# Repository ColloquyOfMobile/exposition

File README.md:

# exposition
Colloquy of Mobiles for exposition in ZKM

## Hardware
- `CAD/KiCad/tj_brain`: **TJ Brain**, one Teensy 4.1 controller per unit (female 1-3, male 1-2, bar).
  It brings back T. J. McLeish's distributed 2018 architecture and has a DA-15 body connector
  compatible with the female harnesses.
- `CAD/KiCad/tj_backplane`: **TJ Backplane**, the 12V / 5V splitter (fused, with LEDs) that feeds the
  brains and the USB hub.
- `CAD/KiCad/electronic box`: the previous centralised board (Arduino Mega + U2D2).
- `Source code/Teensy/tj_brain_test`: Teensy pin map and bring-up test sketch for the TJ Brain.

## Todo
In KiCad:
- Choose the footprint for power supply capacitor.
- Check dimension of jack barrel.

## Todo

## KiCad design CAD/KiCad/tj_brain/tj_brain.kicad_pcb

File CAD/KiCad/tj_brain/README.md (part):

# TJ Brain – one Teensy 4.1 brain per unit

This board brings back the distributed 2018 architecture of T. J. McLeish
(one controller per mobile) with a Teensy 4.1. The **same board** is used for
the three females, the two males and the bar. A DIP switch sets which unit it is.

```
            computer (Python server)
                 │ USB
        7-port powered USB 2.0 hub ───────────────┐ one USB cable per brain
                 │                                │ (Teensy micro-USB)
   12V PSU ──┐   │                                ▼
   5V  PSU ──┴─► TJ BACKPLANE ──Mini-Fit Jr 4p──► TJ BRAIN ×6 (F1 F2 F3 M1 M2 BAR) + spare
                 (fused splitter,                    │
                  powers the hub)                    ├─ DXL1-3 (JST EH) ─ Dynamixel X TTL
                                                     ├─ NP1-4 (pluggable 5.08) ─ NeoPixels
                                                     ├─ SPK, LS1-4, MIC, STATE1-2 (JST XH)
                                                     └─ BODY DA-15 ─ into the female (or male) body
```

* Schematic: `tj_brain.kicad_sch` (9 sheets), PCB: `tj_brain.kicad_pcb`
  (180 × 136 mm, 2 layers, 1.6 mm, 1 oz copper is enough on this board).
* Manufacturing files in `fab/`: Gerbers and drill files (zipped), pick-and-place, BOM,
  schematic PDF, assembly drawing, top and bottom renders.
* Custom parts (Teensy 4.1 socket, SparkFun TPA2005D1 breakout) are in `../tj_library`.
* Everything is generated by `../generator` (see the last section). Edit the generator
  and regenerate rather than editing the KiCad files by hand, or the next run overwrites
  your changes.

## Connectors

| Ref | Connector | Pins |
|-----|-----------|------|
| J1 | Molex Mini-Fit Jr 5569 right-angle 2×2, from the backplane | 1 = +12V, 2 = +5V, 3 = GND, 4 = GND |
| U1 | Teensy 4.1 on 2× 1×24 female headers | USB from the hub goes straight into the Teensy |
| J20 BODY | DA-15 **male** (pins on the board), right-angle | see table below |
| J3–J5 DXL1–3 | JST EH B3B-EH-A (ROBOTIS X-series TTL) | 1 GND, 2 +12V, 3 DATA |
| J6–J9 NP1–4 | Phoenix MSTBA 2,5/3-G-5,08 (plug MSTB 2,5/3-ST-5,08) | 1 +5V, 2 DIN, 3 GND |
| J11 SPK | Phoenix MSTBA 2,5/2-G-5,08 | 1 SPK+, 2 SPK− |
| J13–J16 LS1–4 | JST XH 3p | 1 sensor VCC (5V, or 3V3 via JP4), 2 GND, 3 signal 0–5V |
| J12 MIC | JST XH 3p | 1 VCC (5V, or 3V3 via JP3), 2 GND, 3 MAX9814 OUT |
| J17/J18 STATE1/2 | JST XH 2p | 1 switched +5V through 150 Ω, 2 GND |
| J10 EXT AMP | 1×4 header | 1 line out (AC coupled), 2 GND, 3 +5V, 4 GND |
| J2 EXP | 2×5 header | 3V3, 5V, SDA, SCL, A9, A11, D26, D27, A16, A17 |
| J19 PROBE | 1 pin | logic probe input for the PROBE LED (0–12 V) |

### BODY DA-15 (J20)

Pins 4, 5, 6, 7, 8, 12, 13, 14 and 15 match the female D-subs of the old electronic box
(J1/J5 there). The existing female body harnesses plug in unchanged. Pins 1, 2, 3, 9, 10
and 11 were unused there and now carry what a male body needs.

| Pin | Signal | Female use | Male use |
|----:|--------|------------|----------|
| 1 | LS2 | – | photosensor B |
| 2 | LS3 | – | photosensor C |
| 3 | LS4 | – | photosensor D |
| 4 | SPK− | speaker | speaker |
| 5 | LS1 | photosensor | photosensor A |
| 6 | MIC | microphone module out | microphone module out |
| 7 | +12V (PTC 3 A, F1) | mirror Dynamixel | – |
| 8 | GND | | |
| 9 | NP2 | – | up ring NeoPixels |
| 10 | STATE1 | – | state LED / backlight (switched 5V, 150 Ω) |
| 11 | AUX (analog, clamped) | spare | spare |
| 12 | SPK+ | speaker | speaker |
| 13 | NP1 | body NeoPixel strip | body NeoPixel strip |
| 14 | DXL DATA | mirror Dynamixel | – |
| 15 | +5V (PTC 4 A, F2) | NeoPixels, sensors, mic | NeoPixels, sensors, mic |
| shell | GND | | |

The board side is a **male** DA-15, the same as the footprint in the old electronic box.
Check this against your harness connectors before ordering.

## LEDs

| LED | Meaning |
|-----|---------|
| 12V, 5V, 3V3 | rail present on the board |
| BODY12, BODY5 | rail present on the DA-15 after its PTC (off = PTC tripped) |
| HB, HOST, ERR, USER | driven by firmware (heartbeat, host connected, error, free) |
| NP1–NP4 | data on that NeoPixel output (hardware pulse stretcher, ~50 ms per frame) |
| DXL TX | the Teensy is transmitting on the Dynamixel bus |
| DXL BUS | any traffic on the Dynamixel bus (TX or replies) |
| TONE | tone output active |
| PROBE | free logic probe: touch J19 to any 0–12 V signal |
| LIGHT1–4 | sensor above the threshold set with trimmer TH1–4 (LM339). Use it to aim the beams |
| STATE1, STATE2 | state output switched on (brightness follows PWM) |

## Teensy 4.1 pin map

The pin map is also in `Source code/Teensy/tj_brain_test/tj_brain_pins.h`.

| Pin | Function | Pin | Function |
|----:|----------|----:|----------|
| 0 / 1 | Dynamixel RX1 / TX1 | 14 (A0) | LS1 |
| 2 | Dynamixel DIR (1 = TX) | 15 (A1) | LS2 |
| 3 / 4 | STATE1 / STATE2 (PWM) | 16 (A2) | MIC |
| 5 | AMP_EN (amp shutdown, high = on) | 17 (A3) | LS3 |
| 6, 7, 11, 28 | unit ID bits 0–3 (SW1) | 18 / 19 | SDA / SCL (J2) |
| 8 | NP1 (TX2) | 20 (A6) | LS4 |
| 29 | NP2 (TX7) | 21 (A7) | MSGEQ7 OUT |
| 35 | NP3 (TX8) | 22 (A8) | AUX (DA-15 pin 11) |
| 24 | NP4 (TX6) | 23, 25, 26, 27, 40, 41 | expansion J2 |
| 9 / 10 | MSGEQ7 STROBE / RESET | 30, 31, 32, 37 | LEDs HB, HOST, ERR, USER |
| 12 | AUDIO (tone() or MQSL) | 13, 33, 34, 36, 38, 39 | free (13 = on-board LED) |

The four NeoPixel pins are serial TX pins, so the `WS2812Serial` (DMA, non-blocking) or
`OctoWS2811` libraries can drive them without stopping interrupts. The Dynamixel bus works
with `Dynamixel2Arduino dxl(Serial1, 2);`.

## Unit ID (SW1)

Switch 1 is bit 0, and a switch set to ON counts as 1. The firmware reads it with
`readUnitId()` and reports its role to the host. The host can then open the right serial
port for each unit without having to remember port names.

| ID | Unit | SW1 1-2-3-4 | Dynamixel ids (unchanged) |
|---:|------|-------------|---------------------------|
| 1 | female1 | ON off off off | 1 body, 2 mirror |
| 2 | female2 | off ON off off | 3, 4 |
| 3 | female3 | ON ON off off | 5, 6 |
| 4 | male1 | off off ON off | 7 |
| 5 | male2 | ON off ON off | 8 |
| 6 | bar | off ON ON off | 9 |

## Per-unit build

| | Female 1–3 | Male 1–2 | Bar |
|---|---|---|---|
| Where | static part, DA-15 cable into the rotating body | on the bar / male static part | bar |
| DXL1 | body rotation motor | male rotation motor | bar motor |
| DA-15 DXL | mirror motor (inside the body) | – | – |
| NP1 | body strip, 50 RGBW | body strip, 40 RGBW (ring + drive) | – |
| NP2 | – | up ring, 12 RGBW | – |
| LS1–4 | LS1 | A–D | – |
| MIC / SPK | yes | yes | – |
| STATE1 | – | backlight (KWB-R8445W) | – |
| Tone filter | values for the unit's band | values for the unit's band | – |
| May be left unpopulated | – | – | U5 amp, U6 MSGEQ7, U7 LM339 and their parts |

### Tone filter (R23 = R24, C10 = C11)

These values come from T. Erforth's "Pask redesign" (Table 2). The board default is the
1 kHz set. Fit the set that matches each unit's band.

| Band | R | C |
|-----:|---|---|
| 160 Hz | 2k2 | 470 nF |
| 400 Hz | 2k | 220 nF |
| 1 kHz | 1k2 | 150 nF |
| 2.5 kHz | 1k8 | 47 nF |
| 6.25 kHz | 2k2 | 10 nF |

* If the Teensy generates a sine wave instead (Audio library on MQS pin 12), use
  2k2 / 10 nF for every unit. The filter then only removes the MQS carrier.
* The divider is 22k / 6k8 instead of Thomas's 22k / 3k3. The Teensy swings 3.3 Vpp
  instead of 5 Vpp, so this ratio still gives about 330 mVpp at the amplifier.

### Amplifier options

* **On-board** (default): SparkFun BOB-11044 (TPA2005D1) plugged in at U5, volume on RV1.
  This is the same footprint as the electronic box. AMP_EN can mute it.
* **Amp next to the speaker** (Thomas's recommendation for the class-D EMI):
  1. Leave U5 out.
  2. Close JP1 and JP2. The DA-15 pins 12/4 then carry the line level (AC coupled) and GND.
  3. Power the GF1002 module in the body from DA-15 pin 15 (5V).
  4. Instead of steps 2–3, a module on the board can be wired to the EXT AMP header J10.

### Sensors and microphone

* The light sensor inputs accept 0–5 V modules, as in the old box. A 10k/18k divider keeps
  the ADC below 3.3 V.
* For a bare LDR, the 28 kΩ divider is the pull-down. Wire the LDR between VCC and the
  signal pin.
* Sensor VCC is 5V by default. Cut JP4 and bridge it to the 3V3 side for 3.3 V sensors.
  JP3 does the same for the microphone.
* The microphone input (MAX9814, bias 1.25 V, 2 Vpp) has a 1 kΩ resistor and a BAT54S
  clamp. It goes both to A2 and, through 22 kΩ + 10 nF, to the optional socketed MSGEQ7.
* The MSGEQ7 runs at 3.3 V, so its output fits the ADC. Pin 6 is decoupled with 100 nF
  as the datasheet requires; it is not tied to GND.

## Assembly notes

* **Teensy power**: VIN is fed from +5V through a B5819W Schottky diode. The VIN/VUSB
  trace on the Teensy can stay **uncut**: the diode keeps the backplane 5V and the PC
  USB 5V from feeding each other. The Teensy then runs from whichever supply is higher.
* Mount the Teensy on 2× 1×24 female headers. Its USB connector is at the board edge.
  Use a micro-USB cable with strain relief, and tie the cable to the enclosure.
* All SMD parts are 0805 / SOT-23 / SOIC on the top side with hand-solder pads. The
  MSGEQ7 is socketed.
* PTCs: F1 = Bourns MF-RHT300 (body 12V), F2 = MF-RHT400 (body 5V).
* Before plugging the body in, set the four LIGHT thresholds (TH1–4) with the sensors
  installed.
* Bring-up: flash `Source code/Teensy/tj_brain_test`. It prints the unit ID and all the
  analog inputs, pings Dynamixel ids 1–10, and blinks every activity LED.

## Verification done

* The schematic was exported to a netlist with `kicad-cli` and compared net-by-net with
  the design description. Every net matches.
* KiCad DRC on the PCB (`fab/tj_brain-drc-report.txt`): **0 errors, 0 unconnected pads**.
  52 silkscreen warnings remain (connector outlines past the board edge, a few overlapping
  labels). They are cosmetic.
* All 602 pads on the PCB were compared with the design description; every net matches.
* Not checked: the custom footprints (Teensy 4.1 and SparkFun breakout) against real
  parts, the D-sub gender against the existing harness, and the Mini-Fit orientation in
  the enclosure. Check these on the first board before a full run.

## Regenerating

```
cd CAD/KiCad/generator
python3 make_lib.py            # TJ symbol / footprint library
python3 build_brain_sch.py     # schematic + netlist self-check
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
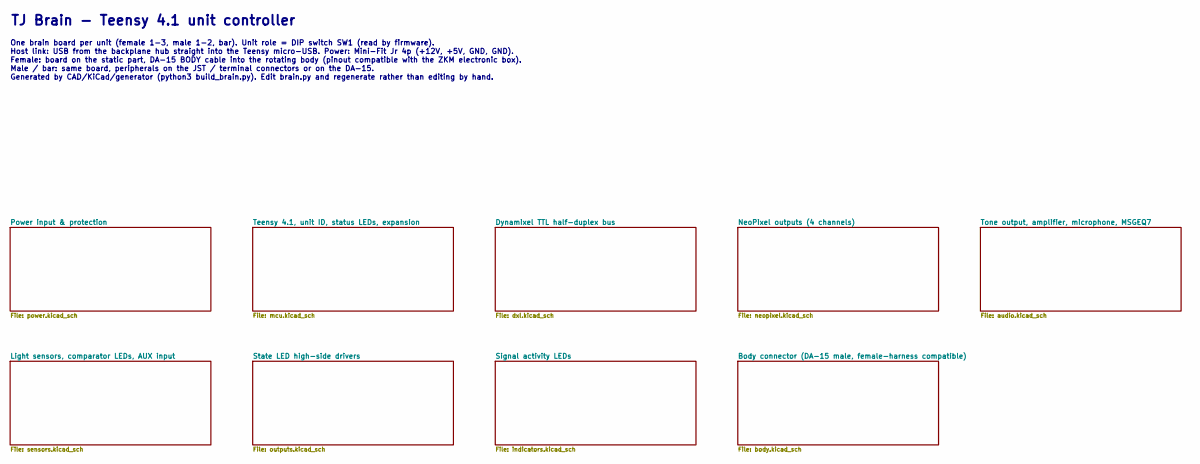
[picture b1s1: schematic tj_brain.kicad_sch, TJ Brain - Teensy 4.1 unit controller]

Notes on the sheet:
TJ Brain - Teensy 4.1 unit controller
One brain board per unit (female 1-3, male 1-2, bar). Unit role = DIP switch SW1 (read by firmware).
Host link: USB from the backplane hub straight into the Teensy micro-USB. Power: Mini-Fit Jr 4p (+12V, +5V, GND, GND).
Female: board on the static part, DA-15 BODY cable into the rotating body (pinout compatible with the ZKM electronic box).
Male / bar: same board, peripherals on the JST / terminal connectors or on the DA-15.
Generated by CAD/KiCad/generator (python3 build_brain.py). Edit brain.py and regenerate rather than editing by hand.

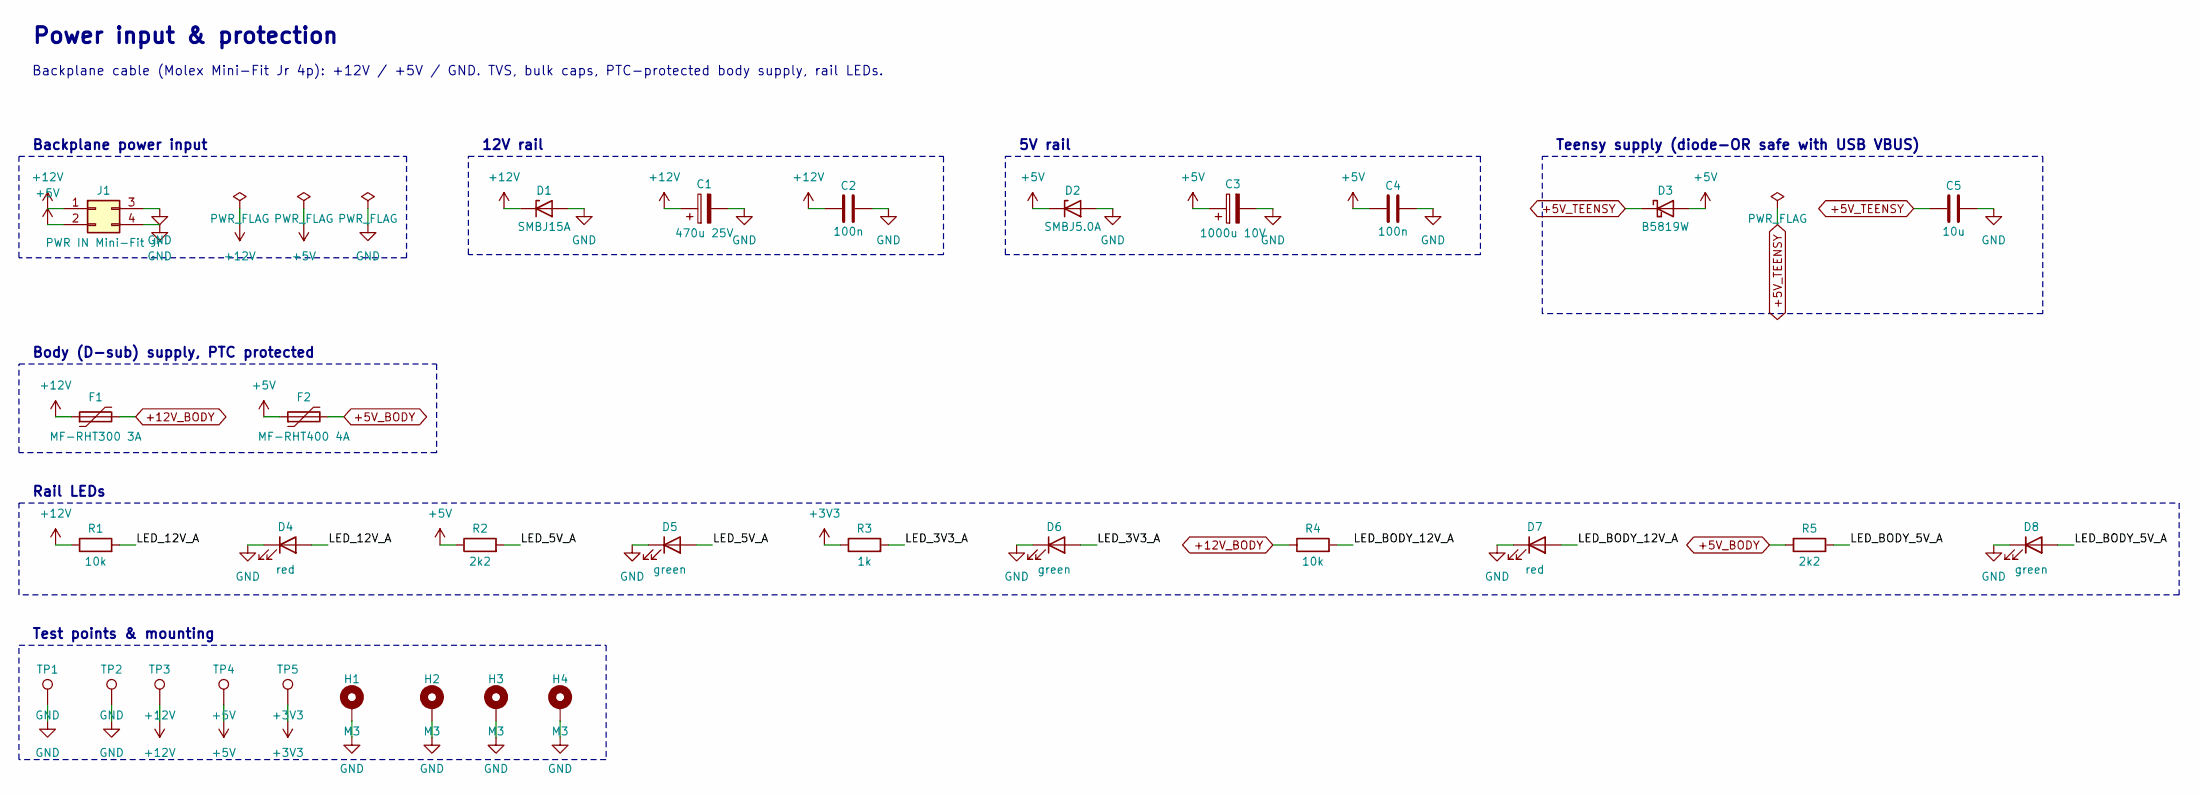
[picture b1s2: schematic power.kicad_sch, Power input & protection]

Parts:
C1: 470u 25V; CP_Radial_D10.0mm_P5.00mm
C2: 100n; C_1206_3216Metric_Pad1.33x1.80mm_HandSolder; Voltage 25V
C3: 1000u 10V; CP_Radial_D10.0mm_P5.00mm
C4: 100n; C_0805_2012Metric_Pad1.18x1.45mm_HandSolder
C5: 10u; C_1206_3216Metric_Pad1.33x1.80mm_HandSolder; Voltage 10V
D1: SMBJ15A; D_SMB
D2: SMBJ5.0A; D_SMB
D3: B5819W; D_SOD-123
D4, D7: red; LED_0805_2012Metric_Pad1.15x1.40mm_HandSolder
D5, D6, D8: green; LED_0805_2012Metric_Pad1.15x1.40mm_HandSolder
F1: MF-RHT300 3A; Fuse_Bourns_MF-RHT300
F2: MF-RHT400 4A; Fuse_Bourns_MF-RHT400
H1, H2, H3, H4: M3; MountingHole_3.2mm_M3_Pad_Via
J1: PWR IN Mini-Fit Jr; Molex_Mini-Fit_Jr_5569-04A1_2x02_P4.20mm_Horizontal; MPN Molex 39-30-1041 (5569-04A1, right angl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
R1, R4: 10k; R_0805_2012Metric_Pad1.20x1.40mm_HandSolder
R2, R5: 2k2; R_0805_2012Metric_Pad1.20x1.40mm_HandSolder
R3: 1k; R_0805_2012Metric_Pad1.20x1.40mm_HandSolder
TP1, TP2: GND; TestPoint_Keystone_5005-5009_Compact
TP3: +12V; TestPoint_Pad_D1.5mm
TP4: +5V; TestPoint_Pad_D1.5mm
TP5: +3V3; TestPoint_Pad_D1.5mm

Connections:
+3V3: R3.1, TP5.1; also elsewhere on the board
+5V: C3.1, C4.1, D2.1 (K), D3.2 (A), F2.1, J1.2, R2.1, TP4.1; also elsewhere on the board
+5V_BODY: F2.2, R5.1; also elsewhere on the board
+5V_TEENSY: C5.1, D3.1 (K); also elsewhere on the board
+12V: C1.1, C2.1, D1.1 (K), F1.1, J1.1, R1.1, TP3.1; also elsewhere on the board
+12V_BODY: F1.2, R4.1; also elsewhere on the board
GND: C1.2, C2.2, C3.2, C4.2, C5.2, D1.2 (A), D2.2 (A), D4.1 (K), D5.1 (K), D6.1 (K), D7.1 (K), D8.1 (K), H1.1, H2.1, H3.1, H4.1, J1.3, J1.4, TP1.1, TP2.1; also elsewhere on the board
LED_3V3_A: D6.2 (A), R3.2
LED_5V_A: D5.2 (A), R2.2
LED_12V_A: D4.2 (A), R1.2
LED_BODY_5V_A: D8.2 (A), R5.2
LED_BODY_12V_A: D7.2 (A), R4.2

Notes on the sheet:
Power input & protection
Backplane cable (Molex Mini-Fit Jr 4p): +12V / +5V / GND. TVS, bulk caps, PTC-protected body supply, rail LEDs.
Backplane power input
12V rail
5V rail
Teensy supply (diode-OR safe with USB VBUS)
Body (D-sub) supply, PTC protected
Rail LEDs
Test points & mounting

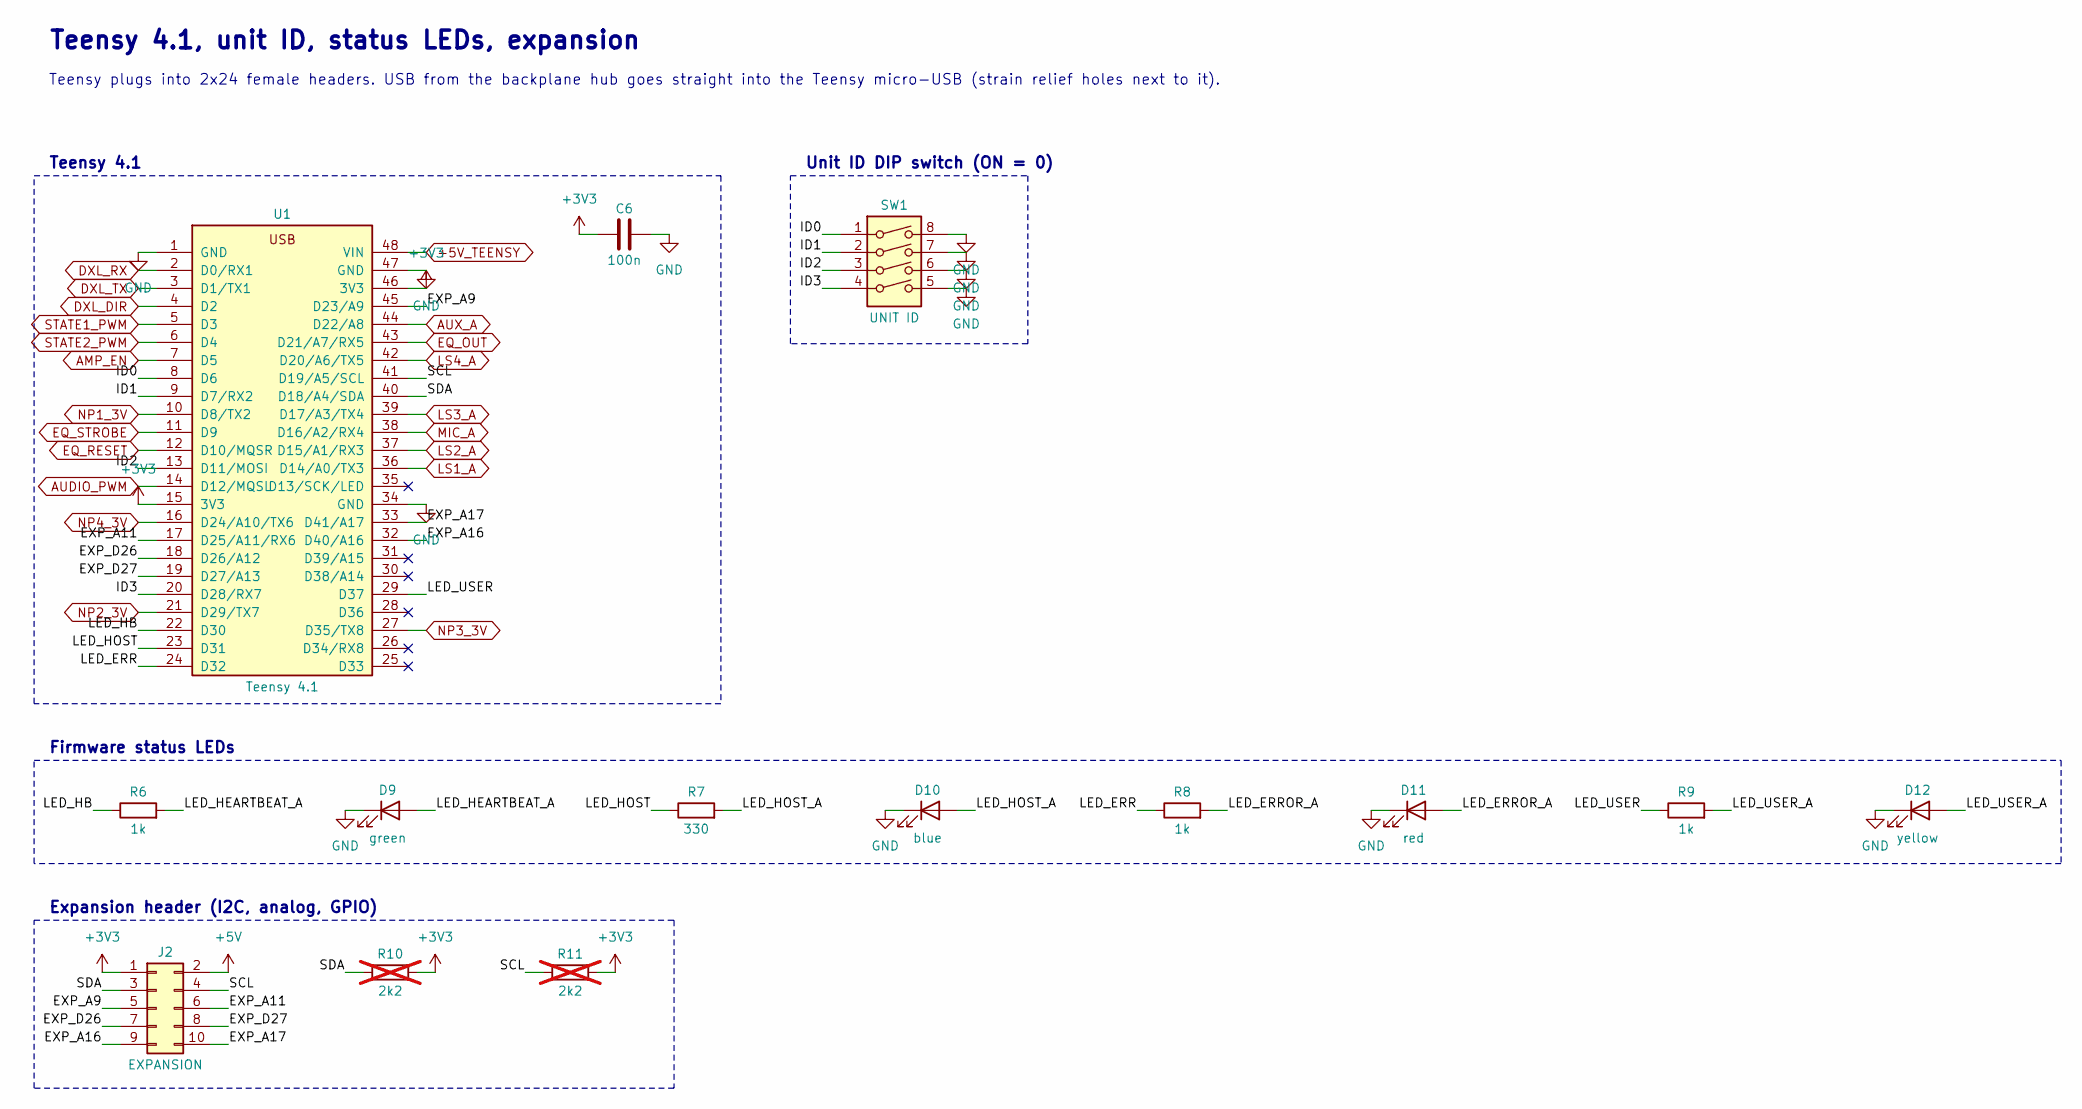
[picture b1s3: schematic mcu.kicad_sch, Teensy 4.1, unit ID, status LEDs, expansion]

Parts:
C6: 100n; C_0805_2012Metric_Pad1.18x1.45mm_HandSolder
D9: green; LED_0805_2012Metric_Pad1.15x1.40mm_HandSolder
D10: blue; LED_0805_2012Metric_Pad1.15x1.40mm_HandSolder
D11: red; LED_0805_2012Metric_Pad1.15x1.40mm_HandSolder
D12: yellow; LED_0805_2012Metric_Pad1.15x1.40mm_HandSolder
J2: EXPANSION; PinHeader_2x05_P2.54mm_Vertical
R6, R8, R9: 1k; R_0805_2012Metric_Pad1.20x1.40mm_HandSolder
R7: 330; R_0805_2012Metric_Pad1.20x1.40mm_HandSolder
R10, R11: 2k2; R_0805_2012Metric_Pad1.20x1.40mm_HandSolder; not fitted
SW1: UNIT ID; SW_DIP_SPSTx04_Slide_9.78x12.34mm_W7.62mm_P2.54mm
U1: Teensy 4.1; Teensy41_Socket; MPN PJRC Teensy 4.1 + 2x 1x24 female header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

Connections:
+3V3: C6.1, J2.1, R10.2, R11.2, U1.15 (3V3), U1.46 (3V3); also elsewhere on the board
+5V: J2.2; also elsewhere on the board
+5V_TEENSY: U1.48 (VIN); also elsewhere on the board
AMP_EN: U1.7 (D5); also elsewhere on the board
AUDIO_PWM: U1.14 (D12/MQSL); also elsewhere on the board
AUX_A: U1.44 (D22/A8); also elsewhere on the board
DXL_DIR: U1.4 (D2); also elsewhere on the board
DXL_RX: U1.2 (D0/RX1); also elsewhere on the board
DXL_TX: U1.3 (D1/TX1); also elsewhere on the board
EQ_OUT: U1.43 (D21/A7/RX5); also elsewhere on the board
EQ_RESET: U1.12 (D10/MQSR); also elsewhere on the board
EQ_STROBE: U1.11 (D9); also elsewhere on the board
EXP_A9: J2.5, U1.45 (D23/A9)
EXP_A11: J2.6, U1.17 (D25/A11/RX6)
EXP_A16: J2.9, U1.32 (D40/A16)
EXP_A17: J2.10, U1.33 (D41/A17)
EXP_D26: J2.7, U1.18 (D26/A12)
EXP_D27: J2.8, U1.19 (D27/A13)
GND: C6.2, D9.1 (K), D10.1 (K), D11.1 (K), D12.1 (K), SW1.5, SW1.6, SW1.7, SW1.8, U1.1 (GND), U1.34 (GND), U1.47 (GND); also elsewhere on the board
ID0: SW1.1, U1.8 (D6)
ID1: SW1.2, U1.9 (D7/RX2)
ID2: SW1.3, U1.13 (D11/MOSI)
ID3: SW1.4, U1.20 (D28/RX7)
LED_ERR: R8.1, U1.24 (D32)
LED_ERROR_A: D11.2 (A), R8.2
LED_HB: R6.1, U1.22 (D30)
LED_HEARTBEAT_A: D9.2 (A), R6.2
LED_HOST: R7.1, U1.23 (D31)
LED_HOST_A: D10.2 (A), R7.2
LED_USER: R9.1, U1.29 (D37)
LED_USER_A: D12.2 (A), R9.2
LS1_A: U1.36 (D14/A0/TX3); also elsewhere on the board
LS2_A: U1.37 (D15/A1/RX3); also elsewhere on the board
LS3_A: U1.39 (D17/A3/TX4); also elsewhere on the board
LS4_A: U1.42 (D20/A6/TX5); also elsewhere on the board
MIC_A: U1.38 (D16/A2/RX4); also elsewhere on the board
NP1_3V: U1.10 (D8/TX2); also elsewhere on the board
NP2_3V: U1.21 (D29/TX7); also elsewhere on the board
NP3_3V: U1.27 (D35/TX8); also elsewhere on the board
NP4_3V: U1.16 (D24/A10/TX6); also elsewhere on the board
SCL: J2.4, R11.1, U1.41 (D19/A5/SCL)
SDA: J2.3, R10.1, U1.40 (D18/A4/SDA)
STATE1_PWM: U1.5 (D3); also elsewhere on the board
STATE2_PWM: U1.6 (D4); also elsewhere on the board

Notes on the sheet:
Teensy 4.1, unit ID, status LEDs, expansion
Teensy plugs into 2x24 female headers. USB from the backplane hub goes straight into the Teensy micro-USB (strain relief holes next to it).
Teensy 4.1
Unit ID DIP switch (ON = 0)
Firmware status LEDs
Expansion header (I2C, analog, GPIO)

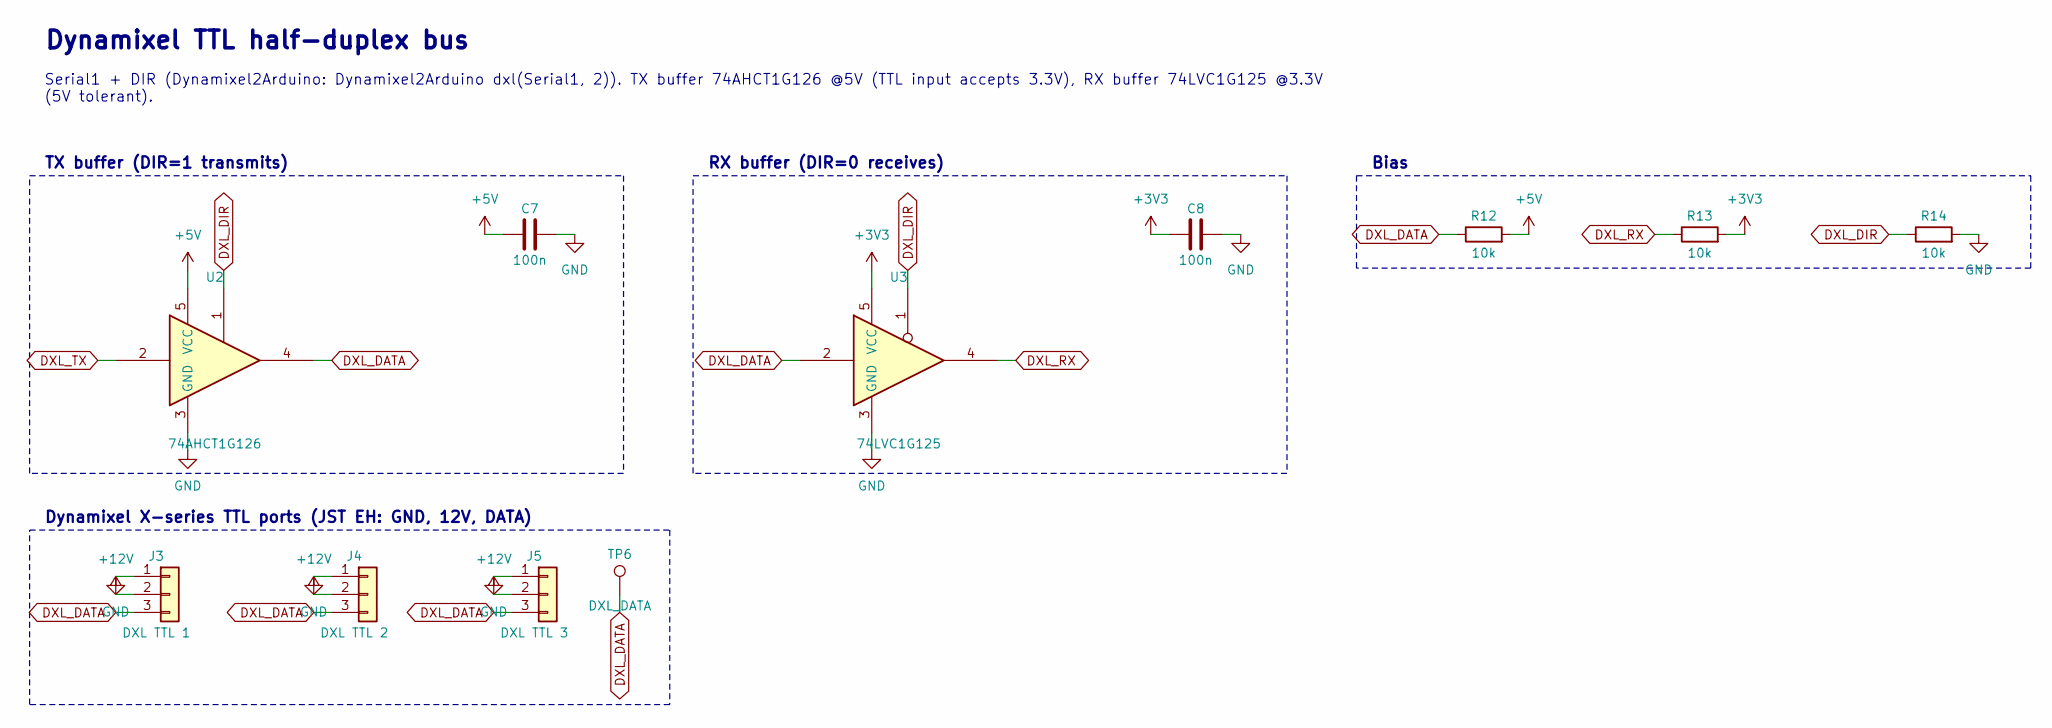
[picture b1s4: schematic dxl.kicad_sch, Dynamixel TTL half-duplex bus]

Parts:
C7, C8: 100n; C_0805_2012Metric_Pad1.18x1.45mm_HandSolder
J3: DXL TTL 1; JST_EH_B3B-EH-A_1x03_P2.50mm_Vertical
J4: DXL TTL 2; JST_EH_B3B-EH-A_1x03_P2.50mm_Vertical
J5: DXL TTL 3; JST_EH_B3B-EH-A_1x03_P2.50mm_Vertical
R12, R13, R14: 10k; R_0805_2012Metric_Pad1.20x1.40mm_HandSolder
TP6: DXL_DATA; TestPoint_Pad_D1.5mm
U2: 74AHCT1G126; SOT-23-5_HandSoldering
U3: 74LVC1G125; SOT-23-5_HandSoldering

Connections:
+3V3: C8.1, R13.2, U3.5 (VCC); also elsewhere on the board
+5V: C7.1, R12.2, U2.5 (VCC); also elsewhere on the board
+12V: J3.2, J4.2, J5.2; also elsewhere on the board
DXL_DATA: J3.3, J4.3, J5.3, R12.1, TP6.1, U2.4, U3.2; also elsewhere on the board
DXL_DIR: R14.1, U2.1, U3.1; also elsewhere on the board
DXL_RX: R13.1, U3.4; also elsewhere on the board
DXL_TX: U2.2; also elsewhere on the board
GND: C7.2, C8.2, J3.1, J4.1, J5.1, R14.2, U2.3 (GND), U3.3 (GND); also elsewhere on the board

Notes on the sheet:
Dynamixel TTL half-duplex bus
Serial1 + DIR (Dynamixel2Arduino: Dynamixel2Arduino dxl(Serial1, 2)). TX buffer 74AHCT1G126 @5V (TTL input accepts 3.3V), RX buffer 74LVC1G125 @3.3V
(5V tolerant).
TX buffer (DIR=1 transmits)
RX buffer (DIR=0 receives)
Bias
Dynamixel X-series TTL ports (JST EH: GND, 12V, DATA)

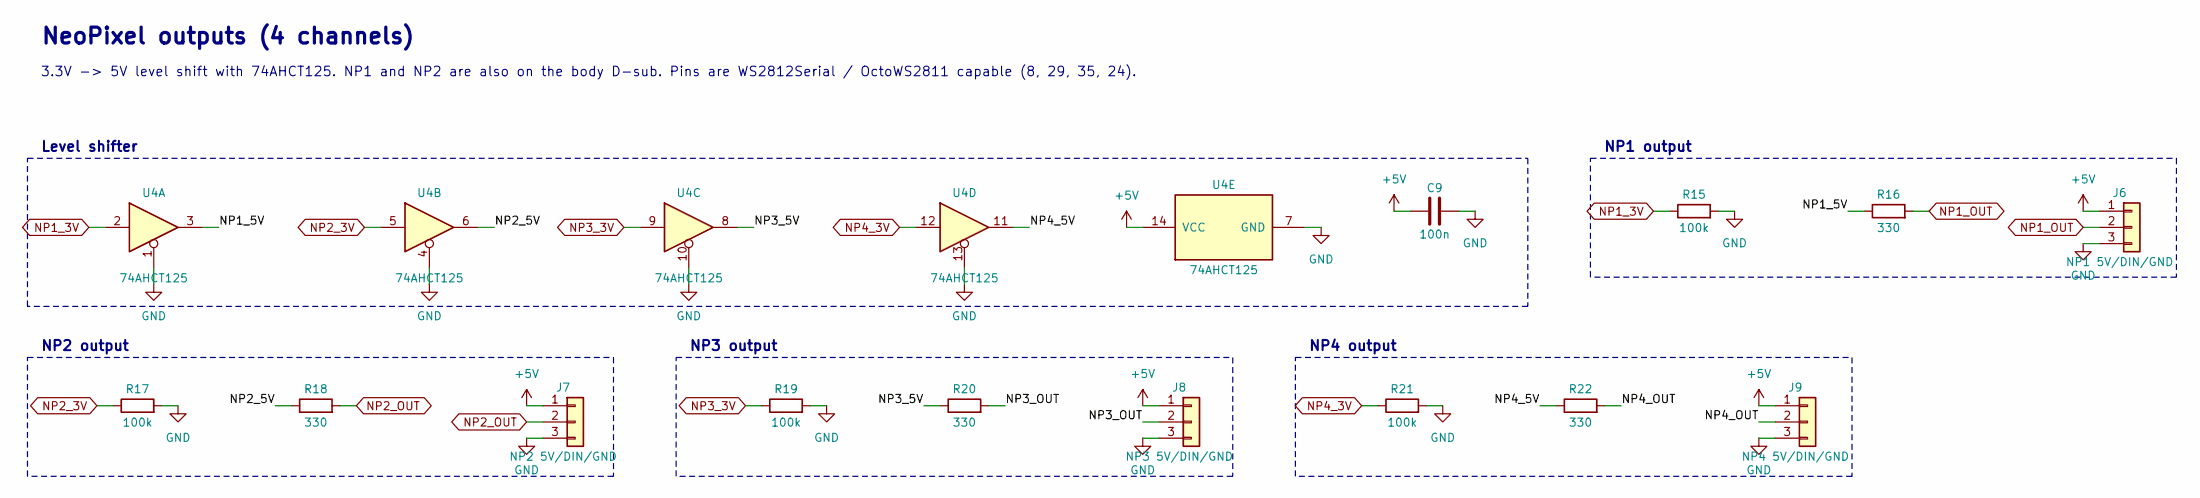
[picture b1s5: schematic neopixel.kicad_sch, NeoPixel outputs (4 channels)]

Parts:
C9: 100n; C_0805_2012Metric_Pad1.18x1.45mm_HandSolder
J6: NP1 5V/DIN/GND; PhoenixContact_MSTBA_2,5_3-G-5,08_1x03_P5.08mm_Horizontal; MPN Phoenix MSTBA 2,5/3-G-5,08 + MSTB 2,5/3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
J7: NP2 5V/DIN/GND; PhoenixContact_MSTBA_2,5_3-G-5,08_1x03_P5.08mm_Horizontal; MPN Phoenix MSTBA 2,5/3-G-5,08 + MSTB 2,5/3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
J8: NP3 5V/DIN/GND; PhoenixContact_MSTBA_2,5_3-G-5,08_1x03_P5.08mm_Horizontal; MPN Phoenix MSTBA 2,5/3-G-5,08 + MSTB 2,5/3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
J9: NP4 5V/DIN/GND; PhoenixContact_MSTBA_2,5_3-G-5,08_1x03_P5.08mm_Horizontal; MPN Phoenix MSTBA 2,5/3-G-5,08 + MSTB 2,5/3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
R15, R17, R19, R21: 100k; R_0805_2012Metric_Pad1.20x1.40mm_HandSolder
R16, R18, R20, R22: 330; R_0805_2012Metric_Pad1.20x1.40mm_HandSolder
U4: 74AHCT125; SOIC-14_3.9x8.7mm_P1.27mm

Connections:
+5V: C9.1, J6.1, J7.1, J8.1, J9.1, U4.14 (VCC); also elsewhere on the board
GND: C9.2, J6.3, J7.3, J8.3, J9.3, R15.2, R17.2, R19.2, R21.2, U4.1, U4.4, U4.7 (GND), U4.10, U4.13; also elsewhere on the board
NP1_3V: R15.1, U4.2; also elsewhere on the board
NP1_5V: R16.1, U4.3
NP1_OUT: J6.2, R16.2; also elsewhere on the board
NP2_3V: R17.1, U4.5; also elsewhere on the board
NP2_5V: R18.1, U4.6
NP2_OUT: J7.2, R18.2; also elsewhere on the board
NP3_3V: R19.1, U4.9; also elsewhere on the board
NP3_5V: R20.1, U4.8
NP3_OUT: J8.2, R20.2
NP4_3V: R21.1, U4.12; also elsewhere on the board
NP4_5V: R22.1, U4.11
NP4_OUT: J9.2, R22.2

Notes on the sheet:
NeoPixel outputs (4 channels)
3.3V -> 5V level shift with 74AHCT125. NP1 and NP2 are also on the body D-sub. Pins are WS2812Serial / OctoWS2811 capable (8, 29, 35, 24).
Level shifter
NP1 output
NP2 output
NP3 output
NP4 output

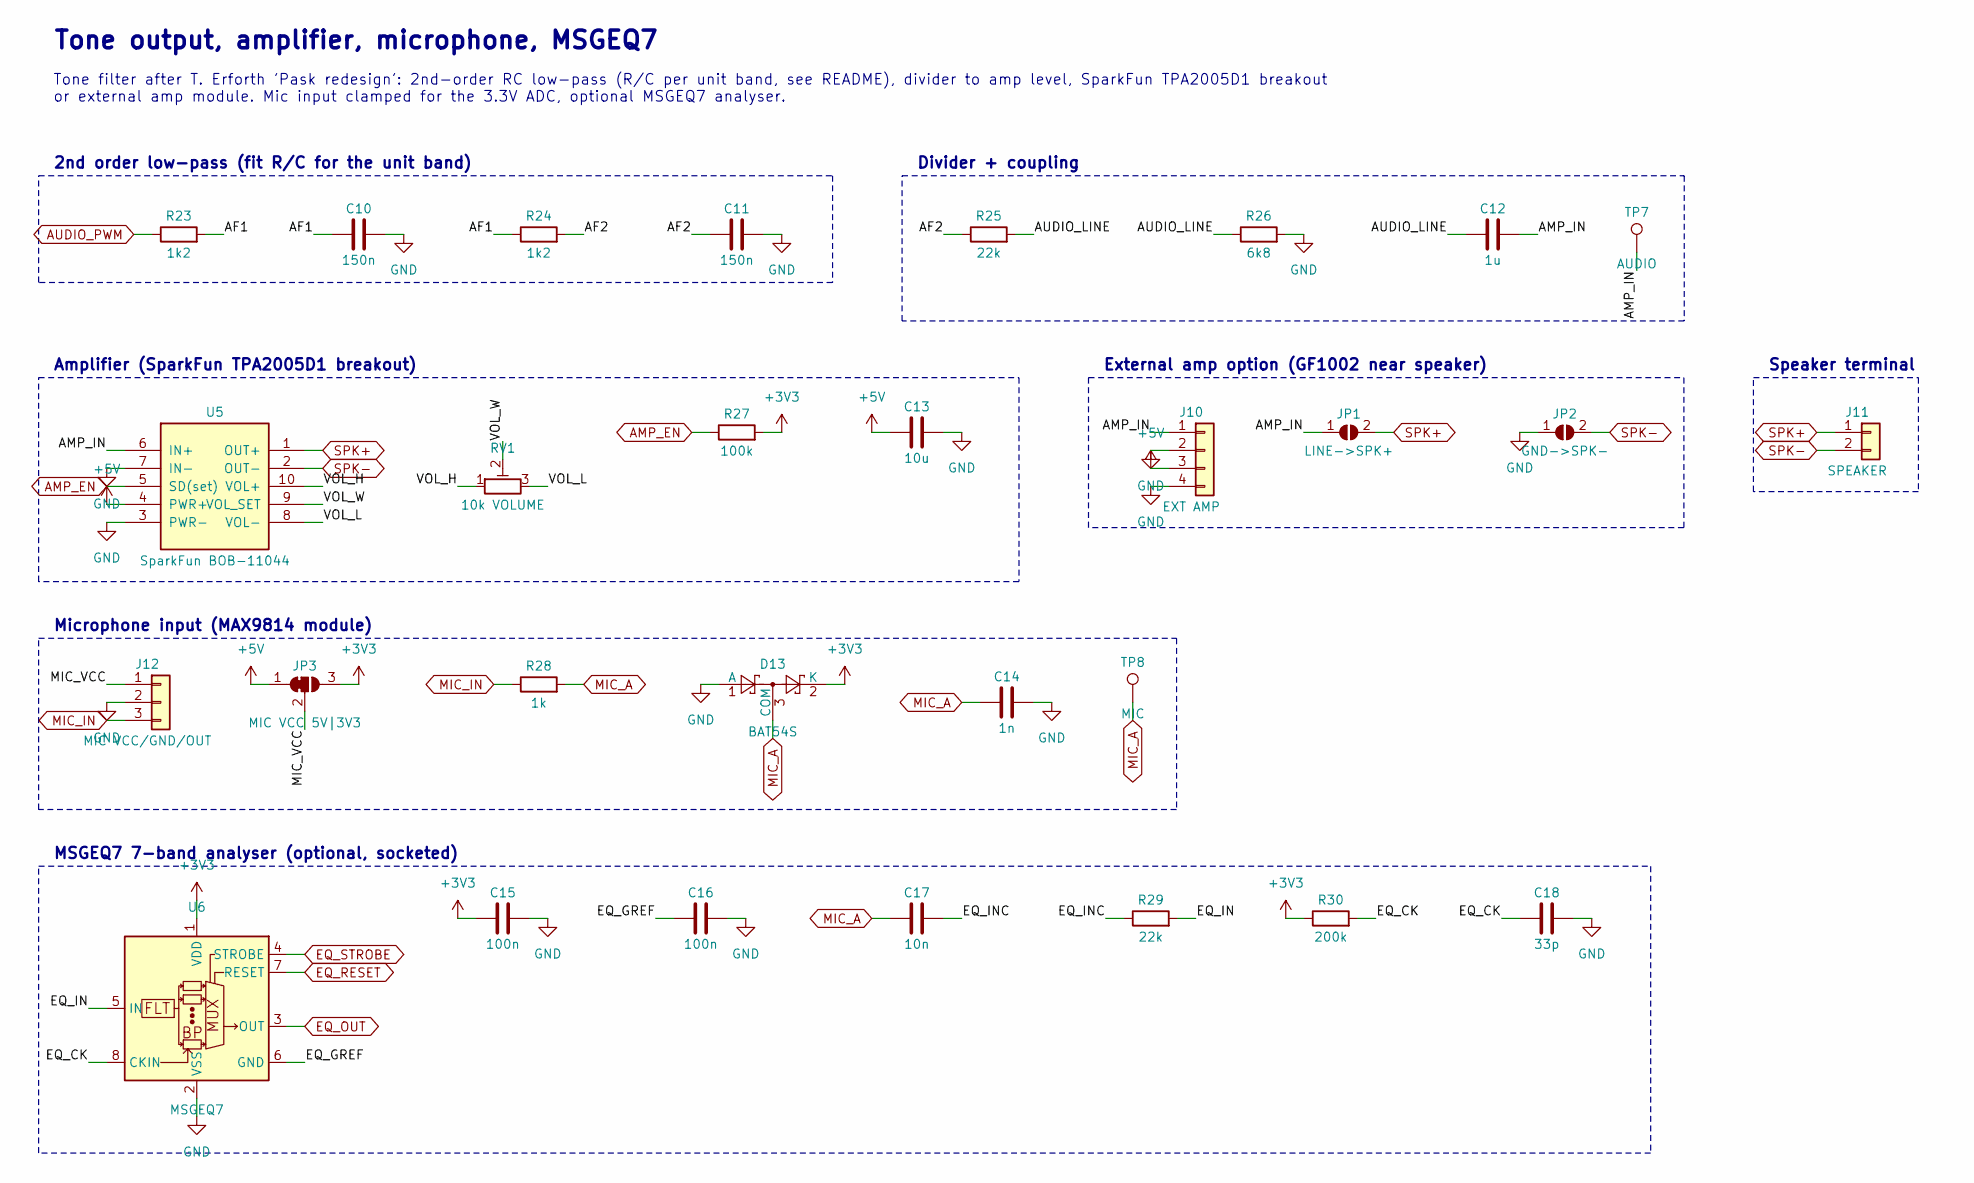
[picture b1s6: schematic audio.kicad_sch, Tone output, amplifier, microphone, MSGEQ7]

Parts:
C10, C11: 150n; C_0805_2012Metric_Pad1.18x1.45mm_HandSolder
C12: 1u; C_0805_2012Metric_Pad1.18x1.45mm_HandSolder
C13: 10u; C_1206_3216Metric_Pad1.33x1.80mm_HandSolder; Voltage 10V
C14: 1n; C_0805_2012Metric_Pad1.18x1.45mm_HandSolder
C15, C16: 100n; C_0805_2012Metric_Pad1.18x1.45mm_HandSolder
C17: 10n; C_0805_2012Metric_Pad1.18x1.45mm_HandSolder
C18: 33p; C_0805_2012Metric_Pad1.18x1.45mm_HandSolder
D13: BAT54S; SOT-23
J10: EXT AMP; PinHeader_1x04_P2.54mm_Vertical
J11: SPEAKER; PhoenixContact_MSTBA_2,5_2-G-5,08_1x02_P5.08mm_Horizontal
J12: MIC VCC/GND/OUT; JST_XH_B3B-XH-A_1x03_P2.50mm_Vertical
JP1: LINE->SPK+; SolderJumper-2_P1.3mm_Open_RoundedPad1.0x1.5mm
JP2: GND->SPK-; SolderJumper-2_P1.3mm_Open_RoundedPad1.0x1.5mm
JP3: MIC VCC 5V|3V3; SolderJumper-3_P1.3mm_Bridged12_RoundedPad1.0x1.5mm
R23, R24: 1k2; R_0805_2012Metric_Pad1.20x1.40mm_HandSolder
R25, R29: 22k; R_0805_2012Metric_Pad1.20x1.40mm_HandSolder
R26: 6k8; R_0805_2012Metric_Pad1.20x1.40mm_HandSolder
R27: 100k; R_0805_2012Metric_Pad1.20x1.40mm_HandSolder
R28: 1k; R_0805_2012Metric_Pad1.20x1.40mm_HandSolder
R30: 200k; R_0805_2012Metric_Pad1.20x1.40mm_HandSolder
RV1: 10k VOLUME; Potentiometer_Bourns_3296W_Vertical
TP7: AUDIO; TestPoint_Pad_D1.5mm
TP8: MIC; TestPoint_Pad_D1.5mm
U5: SparkFun BOB-11044; SparkFun_TPA2005D1_Breakout
U6: MSGEQ7; DIP-8_W7.62mm_Socket

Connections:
+3V3: C15.1, D13.2 (K), JP3.3 (B), R27.2, R30.1, U6.1 (VDD); also elsewhere on the board
+5V: C13.1, J10.3, JP3.1 (A), U5.4 (PWR+); also elsewhere on the board
AF1: C10.1, R23.2, R24.1
AF2: C11.1, R24.2, R25.1
AMP_EN: R27.1, U5.5 (SD(set)); also elsewhere on the board
AMP_IN: C12.2, J10.1, JP1.1 (A), TP7.1, U5.6 (IN+)
AUDIO_LINE: C12.1, R25.2, R26.1
AUDIO_PWM: R23.1; also elsewhere on the board
EQ_CK: C18.1, R30.2, U6.8 (CKIN)
EQ_GREF: C16.1, U6.6 (GND)
EQ_IN: R29.2, U6.5 (IN)
EQ_INC: C17.2, R29.1
EQ_OUT: U6.3 (OUT); also elsewhere on the board
EQ_RESET: U6.7 (RESET); also elsewhere on the board
EQ_STROBE: U6.4 (STROBE); also elsewhere on the board
GND: C10.2, C11.2, C13.2, C14.2, C15.2, C16.2, C18.2, D13.1 (A), J10.2, J10.4, J12.2, JP2.1 (A), R26.2, U5.3 (PWR-), U5.7 (IN-), U6.2 (VSS); also elsewhere on the board
MIC_A: C14.1, C17.1, D13.3 (COM), R28.2, TP8.1; also elsewhere on the board
MIC_IN: J12.3, R28.1; also elsewhere on the board
MIC_VCC: J12.1, JP3.2 (C)
SPK+: J11.1, JP1.2 (B), U5.1 (OUT+); also elsewhere on the board
SPK-: J11.2, JP2.2 (B), U5.2 (OUT-); also elsewhere on the board
VOL_H: RV1.1, U5.10 (VOL+)
VOL_L: RV1.3, U5.8 (VOL-)
VOL_W: RV1.2, U5.9 (VOL_SET)

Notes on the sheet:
Tone output, amplifier, microphone, MSGEQ7
Tone filter after T. Erforth 'Pask redesign': 2nd-order RC low-pass (R/C per unit band, see README), divider to amp level, SparkFun TPA2005D1 breakout
or external amp module. Mic input clamped for the 3.3V ADC, optional MSGEQ7 analyser.
2nd order low-pass (fit R/C for the unit band)
Divider + coupling
Amplifier (SparkFun TPA2005D1 breakout)
External amp option (GF1002 near speaker)
Speaker terminal
Microphone input (MAX9814 module)
MSGEQ7 7-band analyser (optional, socketed)

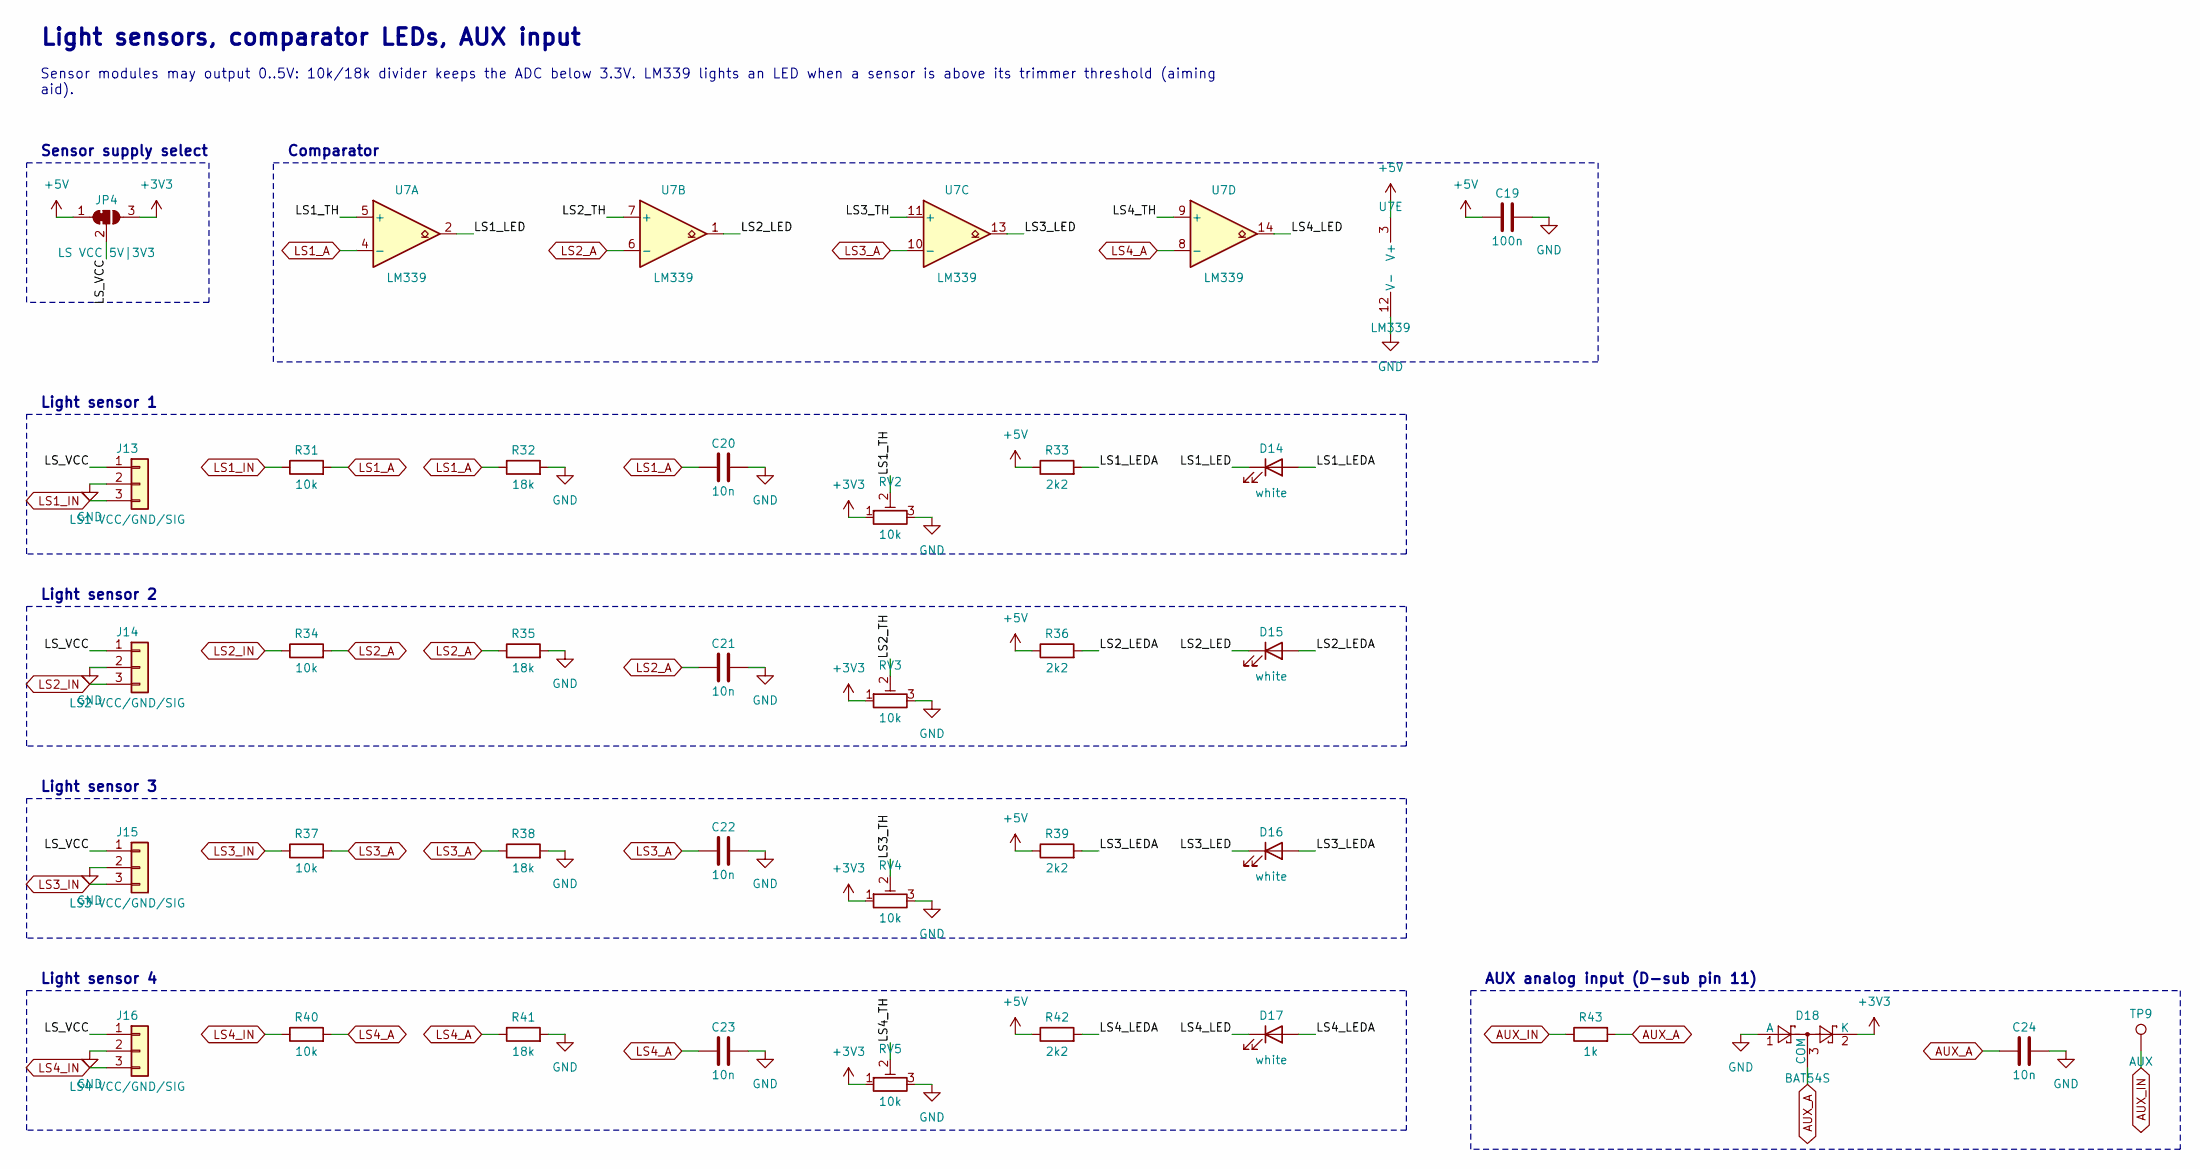
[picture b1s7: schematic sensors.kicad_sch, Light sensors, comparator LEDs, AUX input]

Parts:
C19: 100n; C_0805_2012Metric_Pad1.18x1.45mm_HandSolder
C20, C21, C22, C23, C24: 10n; C_0805_2012Metric_Pad1.18x1.45mm_HandSolder
D14, D15, D16, D17: white; LED_0805_2012Metric_Pad1.15x1.40mm_HandSolder
D18: BAT54S; SOT-23
J13: LS1 VCC/GND/SIG; JST_XH_B3B-XH-A_1x03_P2.50mm_Vertical
J14: LS2 VCC/GND/SIG; JST_XH_B3B-XH-A_1x03_P2.50mm_Vertical
J15: LS3 VCC/GND/SIG; JST_XH_B3B-XH-A_1x03_P2.50mm_Vertical
J16: LS4 VCC/GND/SIG; JST_XH_B3B-XH-A_1x03_P2.50mm_Vertical
JP4: LS VCC 5V|3V3; SolderJumper-3_P1.3mm_Bridged12_RoundedPad1.0x1.5mm
R31, R34, R37, R40: 10k; R_0805_2012Metric_Pad1.20x1.40mm_HandSolder
R32, R35, R38, R41: 18k; R_0805_2012Metric_Pad1.20x1.40mm_HandSolder
R33, R36, R39, R42: 2k2; R_0805_2012Metric_Pad1.20x1.40mm_HandSolder
R43: 1k; R_0805_2012Metric_Pad1.20x1.40mm_HandSolder
RV2, RV3, RV4, RV5: 10k; Potentiometer_Bourns_3296W_Vertical
TP9: AUX; TestPoint_Pad_D1.5mm
U7: LM339; SOIC-14_3.9x8.7mm_P1.27mm

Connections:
+3V3: D18.2 (K), JP4.3 (B), RV2.1, RV3.1, RV4.1, RV5.1; also elsewhere on the board
+5V: C19.1, JP4.1 (A), R33.1, R36.1, R39.1, R42.1, U7.3 (V+); also elsewhere on the board
AUX_A: C24.1, D18.3 (COM), R43.2; also elsewhere on the board
AUX_IN: R43.1, TP9.1; also elsewhere on the board
GND: C19.2, C20.2, C21.2, C22.2, C23.2, C24.2, D18.1 (A), J13.2, J14.2, J15.2, J16.2, R32.2, R35.2, R38.2, R41.2, RV2.3, RV3.3, RV4.3, RV5.3, U7.12 (V-); also elsewhere on the board
LS1_A: C20.1, R31.2, R32.1, U7.4 (-); also elsewhere on the board
LS1_IN: J13.3, R31.1; also elsewhere on the board
LS1_LED: D14.1 (K), U7.2
LS1_LEDA: D14.2 (A), R33.2
LS1_TH: RV2.2, U7.5 (+)
LS2_A: C21.1, R34.2, R35.1, U7.6 (-); also elsewhere on the board
LS2_IN: J14.3, R34.1; also elsewhere on the board
LS2_LED: D15.1 (K), U7.1
LS2_LEDA: D15.2 (A), R36.2
LS2_TH: RV3.2, U7.7 (+)
LS3_A: C22.1, R37.2, R38.1, U7.10 (-); also elsewhere on the board
LS3_IN: J15.3, R37.1; also elsewhere on the board
LS3_LED: D16.1 (K), U7.13
LS3_LEDA: D16.2 (A), R39.2
LS3_TH: RV4.2, U7.11 (+)
LS4_A: C23.1, R40.2, R41.1, U7.8 (-); also elsewhere on the board
LS4_IN: J16.3, R40.1; also elsewhere on the board
LS4_LED: D17.1 (K), U7.14
LS4_LEDA: D17.2 (A), R42.2
LS4_TH: RV5.2, U7.9 (+)
LS_VCC: J13.1, J14.1, J15.1, J16.1, JP4.2 (C)

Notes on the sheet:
Light sensors, comparator LEDs, AUX input
Sensor modules may output 0..5V: 10k/18k divider keeps the ADC below 3.3V. LM339 lights an LED when a sensor is above its trimmer threshold (aiming
aid).
Sensor supply select
Comparator
Light sensor 1
Light sensor 2
Light sensor 3
Light sensor 4
AUX analog input (D-sub pin 11)
